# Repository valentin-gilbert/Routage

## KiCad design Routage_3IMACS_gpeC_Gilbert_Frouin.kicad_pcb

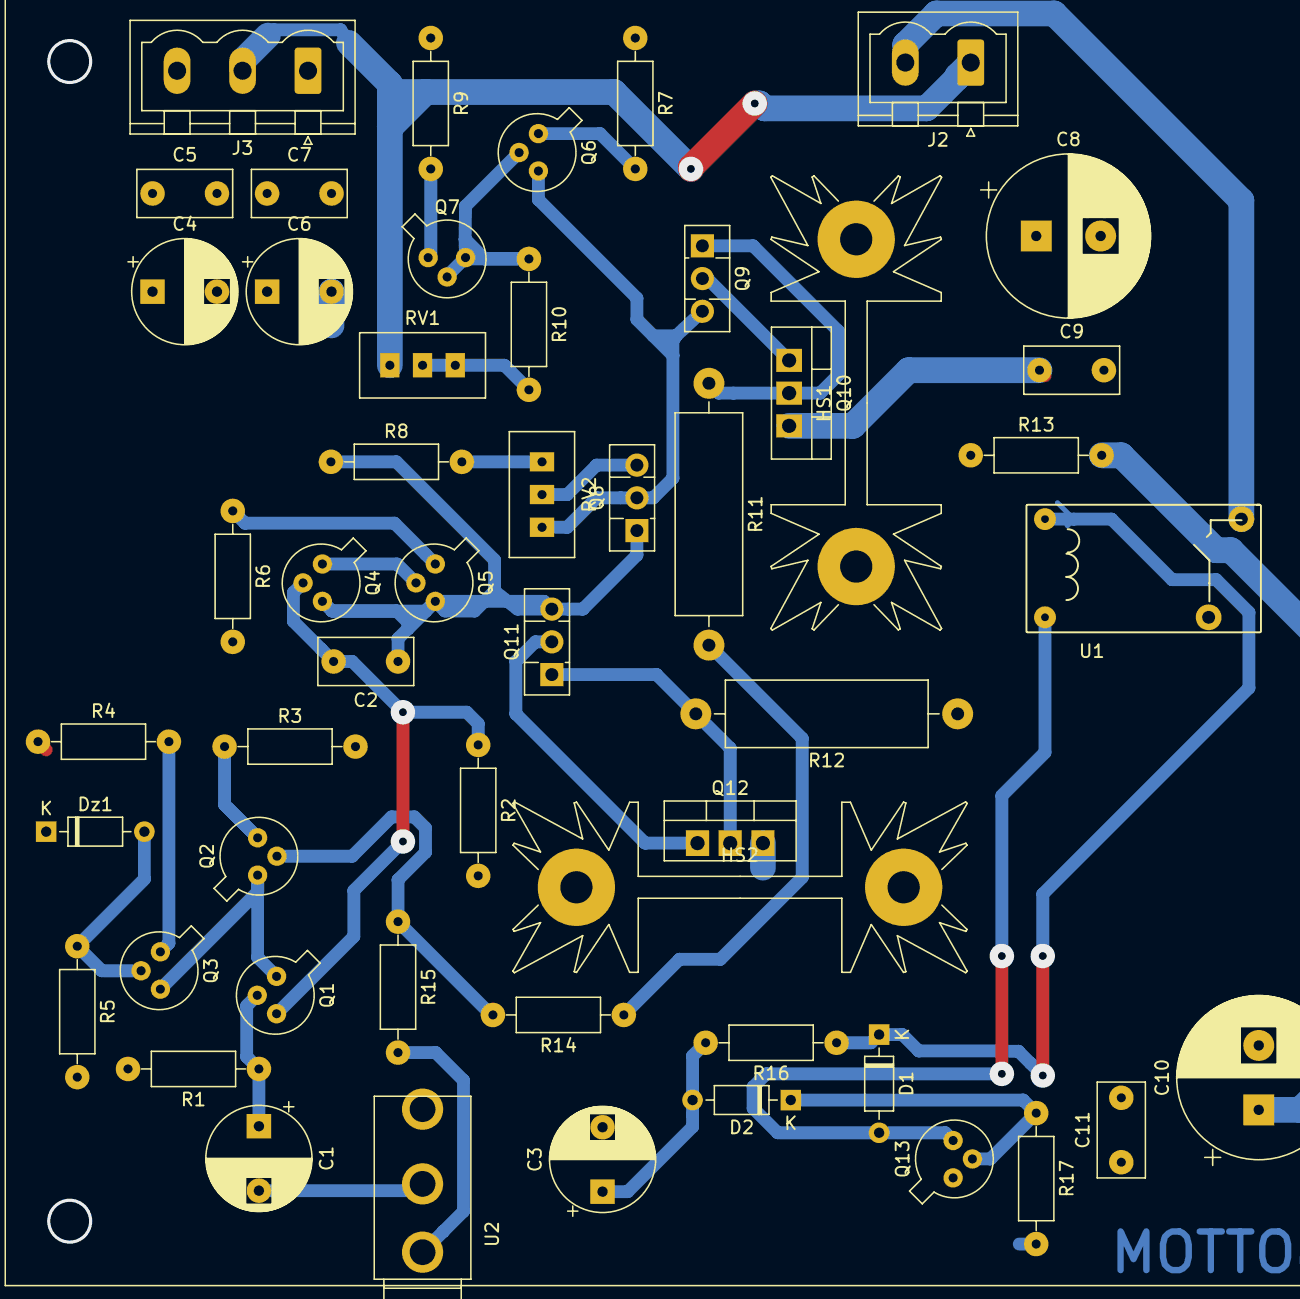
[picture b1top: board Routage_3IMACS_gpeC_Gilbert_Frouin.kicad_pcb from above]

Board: 2 copper layers, 52 parts (0 on the bottom side), 30 nets.

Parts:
C1, C3: 47u; CP_Radial_D8.0mm_P5.00mm
C2: C; C_Rect_L7.2mm_W3.5mm_P5.00mm_FKS2_FKP2_MKS2_MKP2
C4, C6: 10u; CP_Radial_D8.0mm_P5.00mm
C5, C7, C9, C11: 100n; C_Rect_L7.2mm_W3.5mm_P5.00mm_FKS2_FKP2_MKS2_MKP2
C8, C10: 470u; CP_Radial_D12.5mm_P5.00mm
D1, D2: 1N4148; D_DO-35_SOD27_P7.62mm_Horizontal
Dz1: BZx55C5V1; D_DO-35_SOD27_P7.62mm_Horizontal
HS1, HS2: Heatsink; Heatsink_Fischer_SK104-STC-STIC_35x13mm_2xDrill2.5mm
J2: Conn_01x02; PhoenixContact_MSTBVA_2,5_2-G-5,08_1x02_P5.08mm_Vertical
J3: Conn_01x03; PhoenixContact_MSTBVA_2,5_3-G-5,08_1x03_P5.08mm_Vertical
Q1, Q2, Q3, Q6, Q7: 2N2907; TO-18-3
Q4, Q5, Q13: 2N2222; TO-18-3
Q8, Q9: BD139; TO-126-3_Vertical
Q10, Q12: TIP31; TO-220-3_Vertical
Q11: BD138; TO-126-3_Vertical
R1, R8, R13, R14, R15, R16, R17: R; R_Axial_DIN0207_L6.3mm_D2.5mm_P10.16mm_Horizontal
R2, R3: 14.4K; R_Axial_DIN0207_L6.3mm_D2.5mm_P10.16mm_Horizontal
R4: 18K; R_Axial_DIN0207_L6.3mm_D2.5mm_P10.16mm_Horizontal
R5: 1380; R_Axial_DIN0207_L6.3mm_D2.5mm_P10.16mm_Horizontal
R6: 15; R_Axial_DIN0207_L6.3mm_D2.5mm_P10.16mm_Horizontal
R7, R9: 150; R_Axial_DIN0207_L6.3mm_D2.5mm_P10.16mm_Horizontal
R10: 700; R_Axial_DIN0207_L6.3mm_D2.5mm_P10.16mm_Horizontal
R11, R12: R; R_Axial_DIN0516_L15.5mm_D5.0mm_P20.32mm_Horizontal
RV1, RV2: R_POT; Potentiometer_Bourns_3296W_Vertical
U1: Relay_1CT; Relais_112LMH2
U2: Jack_Mono

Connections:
+12V: C4.1, C5.1, C8.1, C9.1, D1.1, Dz1.1, J3.3, Q10.3, R4.1, R7.1, R9.1, R16.1, U1.b2
-12V: C3.2, C6.2, C7.2, C10.2, C11.2, J3.1, Q12.3, R2.2, R3.2, R6.2
/JC1: C1.2, U2.T
GND: C4.2, C5.2, C6.1, C7.1, C8.2, C9.2, C10.1, C11.1, J2.1, J3.2, Q13.1, R1.2, R5.2, R13.2, R15.2, R17.2, RV1.3, U2.G
unnamed: C1.1, Q1.2, R1.1
unnamed: C2.1, Q4.3, Q5.3, Q8.1, Q11.3, R8.1
unnamed: C2.2, Q1.3, Q4.2, R2.1
unnamed: C3.1, D2.2, R16.2
unnamed: D1.2, Q13.3, U1.b1
unnamed: D2.1, Q13.2, R17.1
unnamed: Dz1.2, Q3.2, R5.1
unnamed: J2.2, U1.c2
unnamed: Q1.1, Q2.1, Q3.3
unnamed: Q2.2, R14.2, R15.1
unnamed: Q2.3, R3.1
unnamed: Q3.1, R4.2
unnamed: Q4.1, Q5.2
unnamed: Q5.1, R6.1
unnamed: Q6.1, R7.2
unnamed: Q6.2, Q7.2, Q7.3, R10.1
unnamed: Q6.3, Q8.2, Q9.3, RV2.1
unnamed: Q7.1, R9.2
unnamed: Q8.3, RV2.2
unnamed: Q9.2, Q10.1
unnamed: Q9.1, Q10.2, R11.1
unnamed: Q11.1, Q12.2, R12.2
unnamed: Q11.2, Q12.1
unnamed: R8.2, RV2.3
unnamed: R10.2, RV1.1, RV1.2
unnamed: R11.2, R12.1, R13.1, R14.1, U1.c1

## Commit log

2020-04-15 etape1
2020-04-15 etape2
2020-04-15 Etape3
2020-04-18 Etape4
